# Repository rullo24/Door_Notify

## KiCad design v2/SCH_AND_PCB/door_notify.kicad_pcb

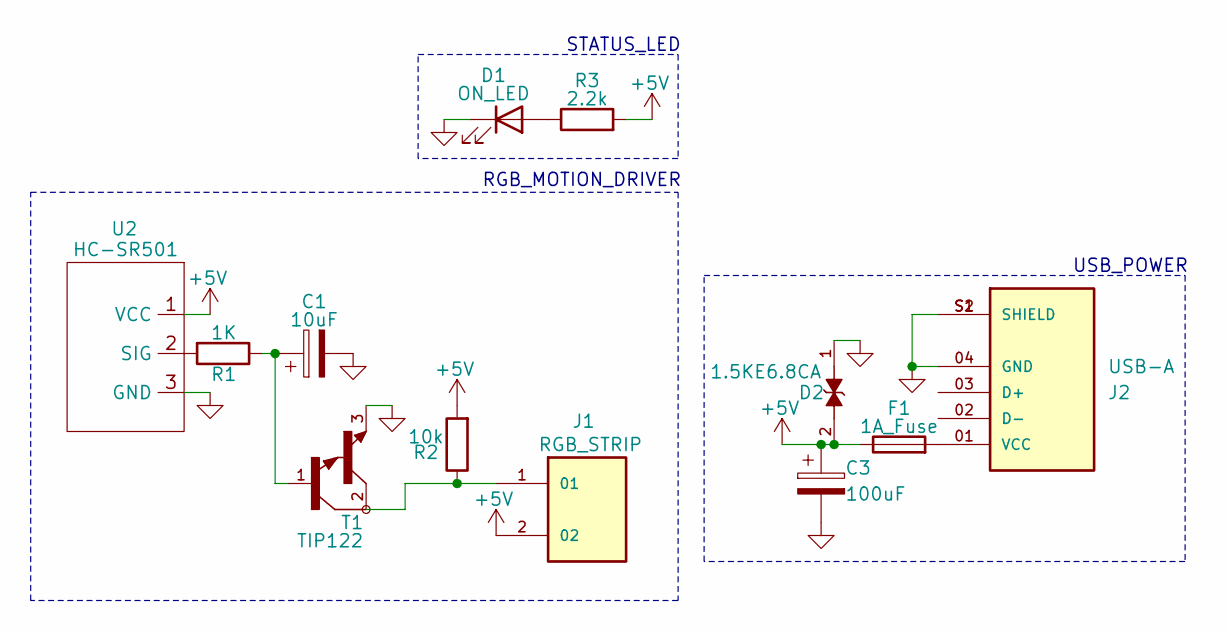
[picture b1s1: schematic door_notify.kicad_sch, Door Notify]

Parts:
C1: 10uF; CP_Radial_D5.0mm_P2.50mm
C3: 100uF; CP_Radial_D5.0mm_P2.50mm
D1: ON_LED; LED_D5.0mm
D2: 1.5KE6.8CA; DIOAD1586W101L900D530; PARTREV O2104
F1: 1A_Fuse; Fuseholder_Cylinder-5x20mm_Schurter_0031_8201_Horizontal_Op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
J1: RGB_STRIP; EBBA-02-C-SS-BU
J2: USB-A; SAMTEC_USB-AM-S-X-X-TH; PARTREV U
R1: 1K; R_Axial_DIN0207_L6.3mm_D2.5mm_P10.16mm_Horizontal
R2: 10k; R_Axial_DIN0207_L6.3mm_D2.5mm_P10.16mm_Horizontal
R3: 2.2k; R_Axial_DIN0207_L6.3mm_D2.5mm_P10.16mm_Horizontal
T1: TIP122
U2: HC-SR501; PinHeader_1x03_P2.54mm_Vertical

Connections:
+5V: C3.1, D2.2, F1.1, J1.2, R2.2, R3.2, U2.1 (VCC)
GND: C1.2, C3.2, D1.1 (K), D2.1, J2.04 (GND), J2.S1 (SHIELD), J2.S2 (SHIELD), T1.3, U2.3 (GND)
unnamed: C1.1, R1.1, T1.1
unnamed: D1.2 (A), R3.1
unnamed: J1.1, R2.1, T1.2
unnamed: F1.2, J2.01 (VCC)
unnamed: R1.2, U2.2 (SIG)

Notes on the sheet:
STATUS_LED
RGB_MOTION_DRIVER
USB_POWER

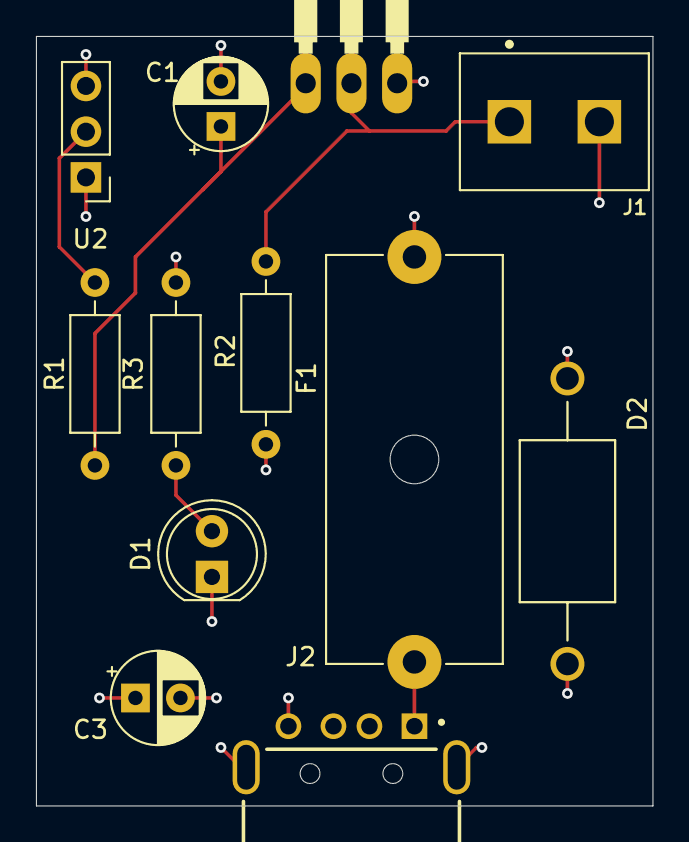
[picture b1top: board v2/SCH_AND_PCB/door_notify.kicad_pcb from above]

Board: 4 copper layers, 34.2 x 42.8 mm, 12 parts (0 on the bottom side), 7 nets.

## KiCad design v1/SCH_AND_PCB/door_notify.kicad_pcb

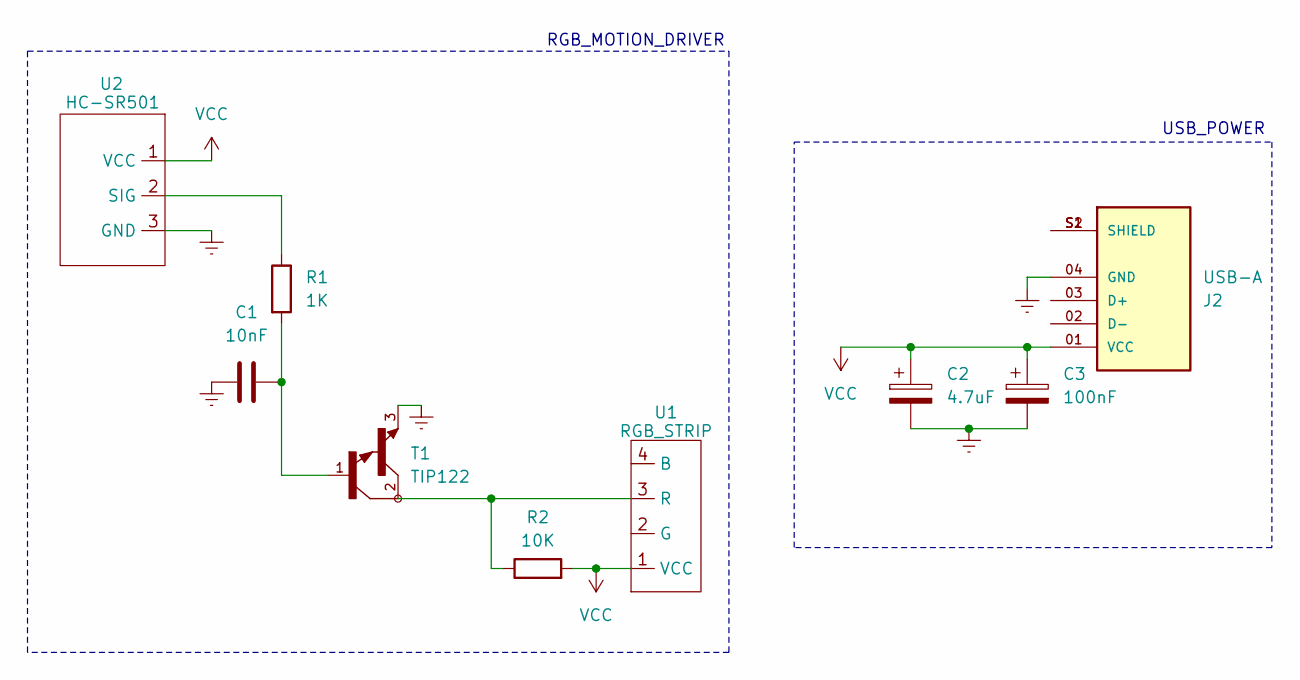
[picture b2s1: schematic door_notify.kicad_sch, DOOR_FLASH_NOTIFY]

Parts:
C1: 10nF; C_Disc_D5.0mm_W2.5mm_P2.50mm
C2: 4.7uF; CP_Radial_D5.0mm_P2.50mm
C3: 100nF; CP_Radial_D5.0mm_P2.50mm
J2: USB-A; SAMTEC_USB-AM-S-X-X-TH; PARTREV U
R1: 1K; R_Axial_DIN0207_L6.3mm_D2.5mm_P10.16mm_Horizontal
R2: 10K; R_Axial_DIN0207_L6.3mm_D2.5mm_P10.16mm_Horizontal
T1: TIP122
U1: RGB_STRIP; PinHeader_1x04_P1.00mm_Vertical
U2: HC-SR501; PinHeader_1x03_P1.00mm_Vertical

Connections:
GNDREF: C1.1, C2.2, C3.2, J2.04 (GND), T1.3, U2.3 (GND)
unnamed: C1.2, R1.2, T1.1
unnamed: J2.S1 (SHIELD), J2.S2 (SHIELD)
unnamed: R2.1, T1.2, U1.3 (R)
unnamed: R1.1, U2.2 (SIG)
VCC: C2.1, C3.1, J2.01 (VCC), R2.2, U1.1 (VCC), U2.1 (VCC)

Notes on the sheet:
RGB_MOTION_DRIVER
USB_POWER

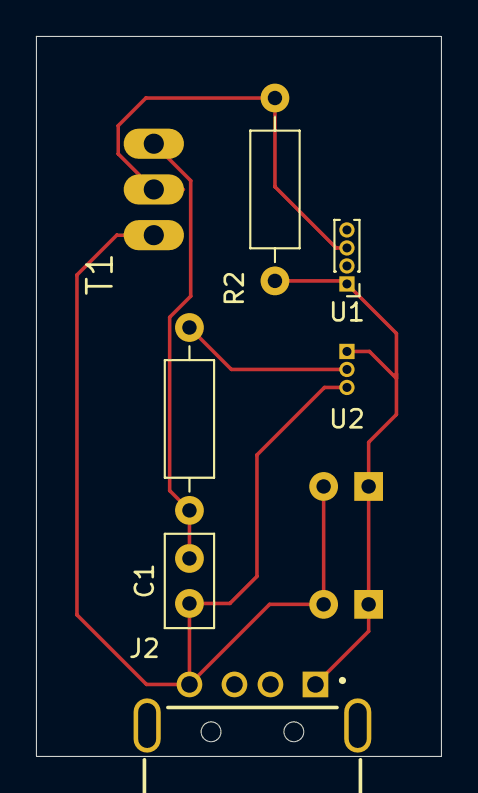
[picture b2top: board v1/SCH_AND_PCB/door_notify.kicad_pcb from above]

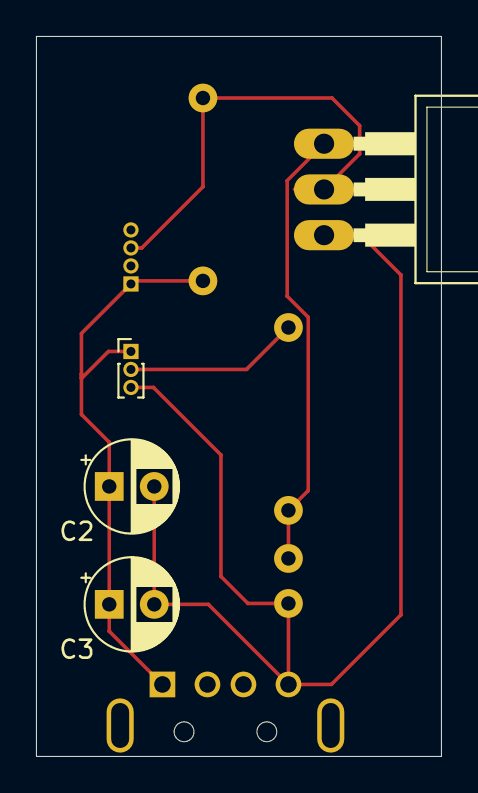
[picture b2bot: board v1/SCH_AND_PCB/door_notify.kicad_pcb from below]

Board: 2 copper layers, 22.5 x 40.0 mm, 9 parts (4 on the bottom side), 6 nets.

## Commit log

2024-10-25 v2 completed
